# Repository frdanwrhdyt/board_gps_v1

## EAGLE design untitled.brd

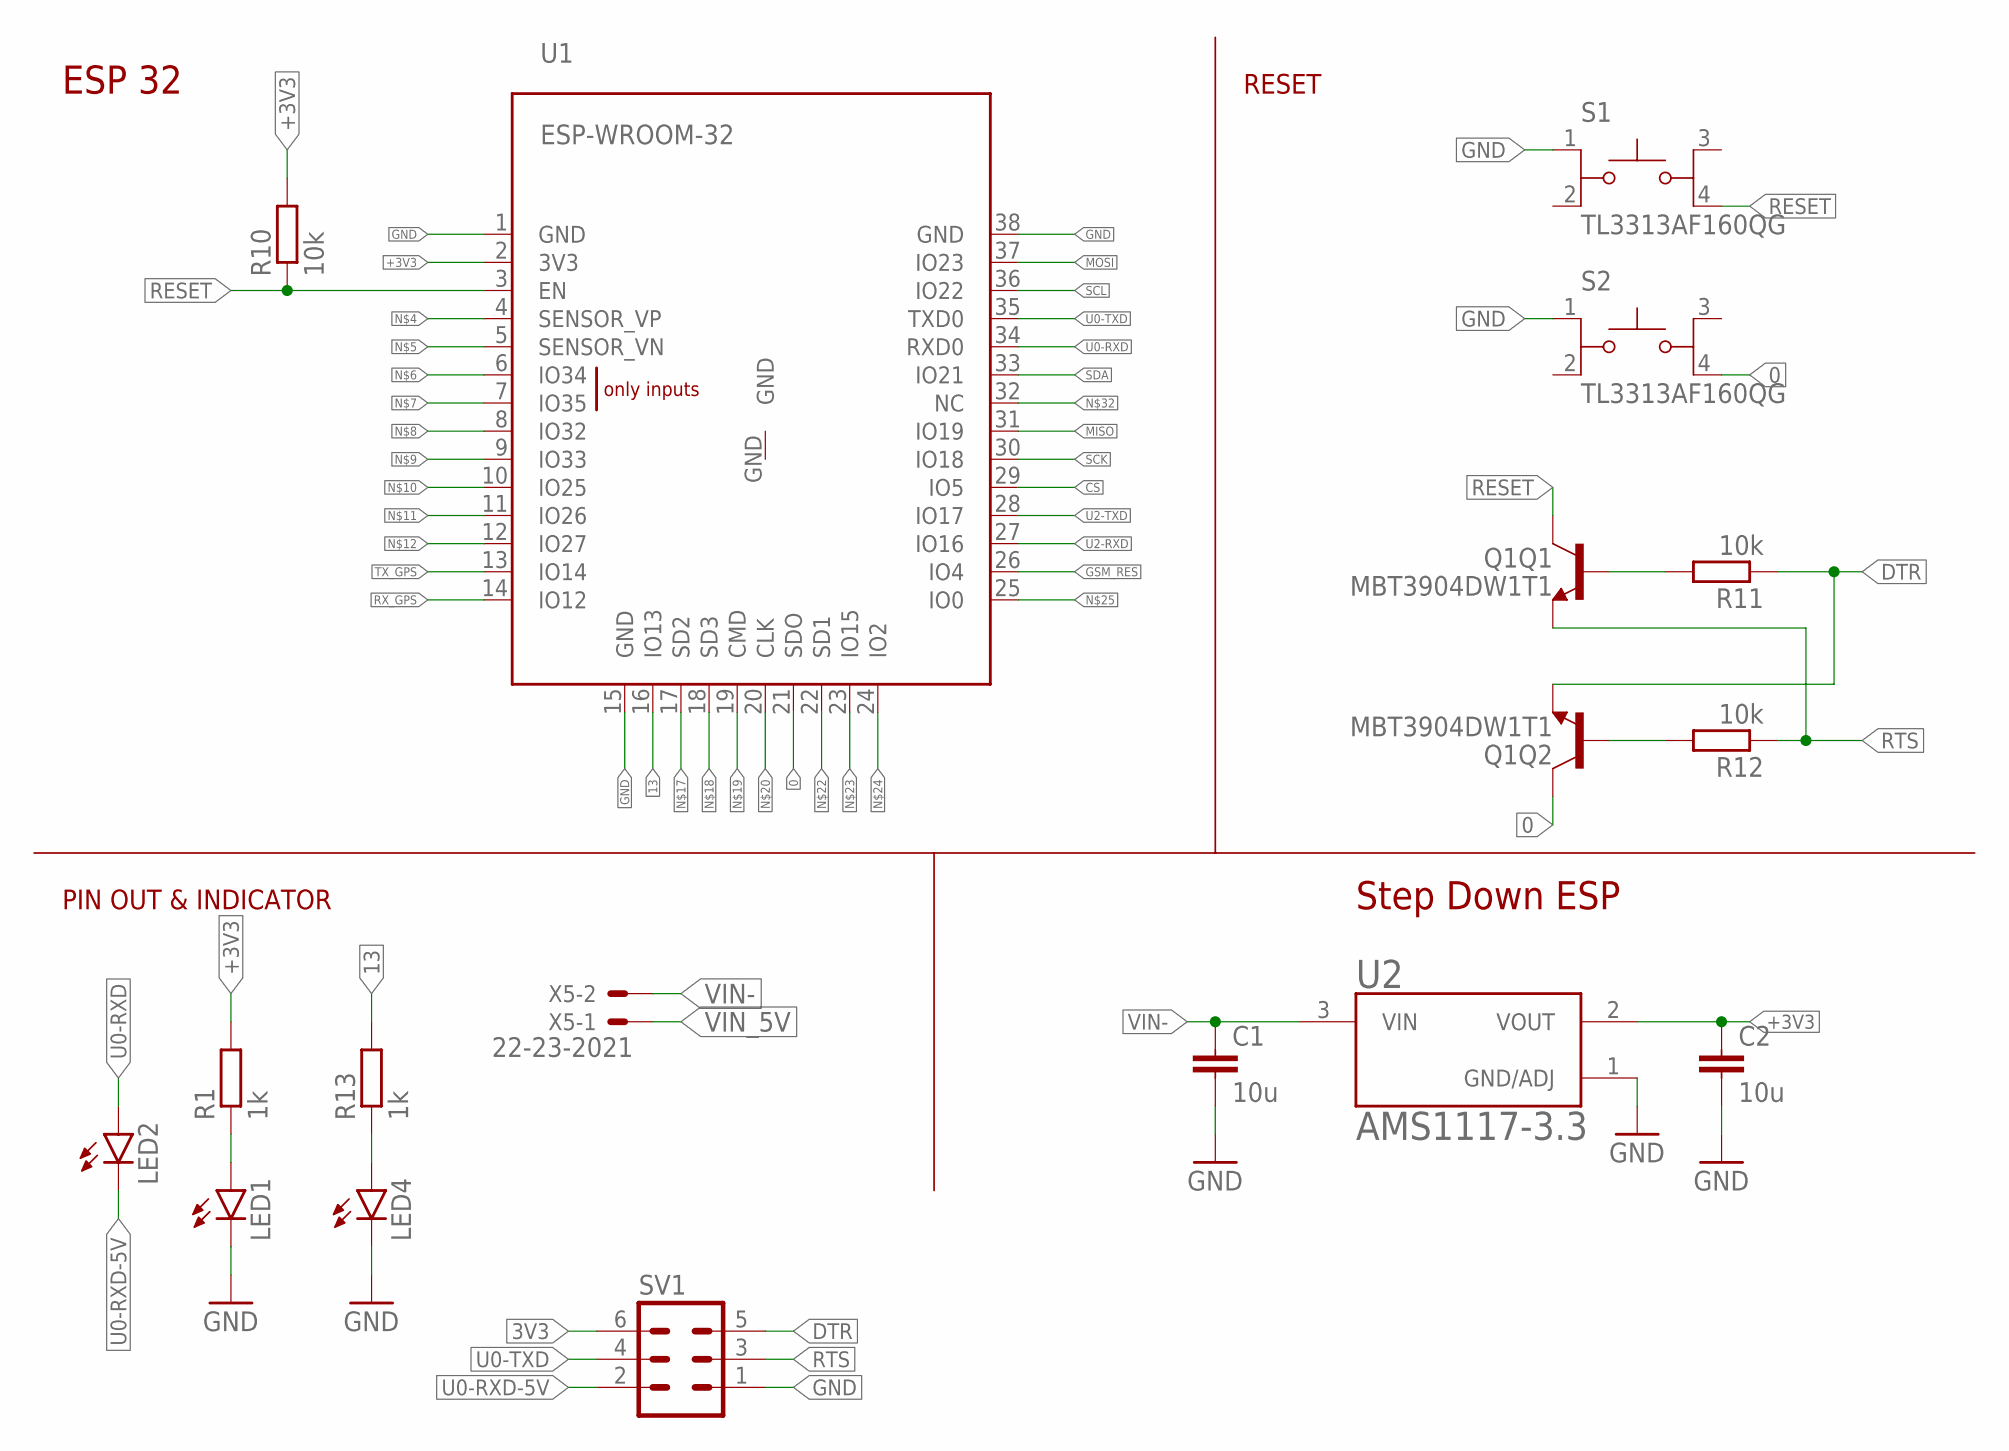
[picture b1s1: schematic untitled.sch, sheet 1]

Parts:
C1, C2: 10u; C0805K
LED1, LED2, LED4: LEDCHIPLED_0805; CHIPLED_0805
Q1: MBT3904DW1T1; SC70-6
R1, R13: 1k; M0805
R10, R11, R12: 10k; M0805
S1, S2: TL3313AF160QG; SW_TL3313AF160QG
SV1: MA03-2
U1: ESP-WROOM-32
U2: AMS1117-3.3; SOT229P700X180-4N
X5: 22-23-2021

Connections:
0: Q1.6 (C), S2.4, U1.21 (SDO)
3V3: SV1.6
13: R13.2, U1.16 (IO13)
+3V3: C2.1, R1.2, R10.2, U1.2 (3V3), U2.2 (VOUT)
CS: U1.29 (IO5); also elsewhere on the board
DTR: Q1.1 (E), R11.1, SV1.5
GND: C1.2, C2.2, LED1.C, LED4.C, S1.1, S2.1, SV1.1, U1.1 (GND), U1.15 (GND), U1.38 (GND), U2.1 (GND/ADJ); also elsewhere on the board
GSM_RES: U1.26 (IO4); also elsewhere on the board
MISO: U1.31 (IO19); also elsewhere on the board
MOSI: U1.37 (IO23); also elsewhere on the board
unnamed: LED1.A, R1.1
unnamed: LED4.A, R13.1
unnamed: Q1.2 (B), R12.2
unnamed: Q1.5 (B), R11.2
RESET: Q1.3 (C), R10.1, S1.4, U1.3 (EN)
RTS: Q1.4 (E), R12.1, SV1.3
RX_GPS: U1.14 (IO12); also elsewhere on the board
SCK: U1.30 (IO18); also elsewhere on the board
SCL: U1.36 (IO22); also elsewhere on the board
SDA: U1.33 (IO21); also elsewhere on the board
TX_GPS: U1.13 (IO14); also elsewhere on the board
U0-RXD: LED2.A, U1.34 (RXD0)
U0-RXD-5V: LED2.C, SV1.2
U0-TXD: SV1.4, U1.35 (TXD0)
U2-RXD: U1.27 (IO16); also elsewhere on the board
U2-TXD: U1.28 (IO17); also elsewhere on the board
VIN-: C1.1, U2.3 (VIN), X5.2; also elsewhere on the board
VIN_5V: X5.1; also elsewhere on the board

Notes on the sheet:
Step Down ESP
ESP 32
RESET
PIN OUT & INDICATOR

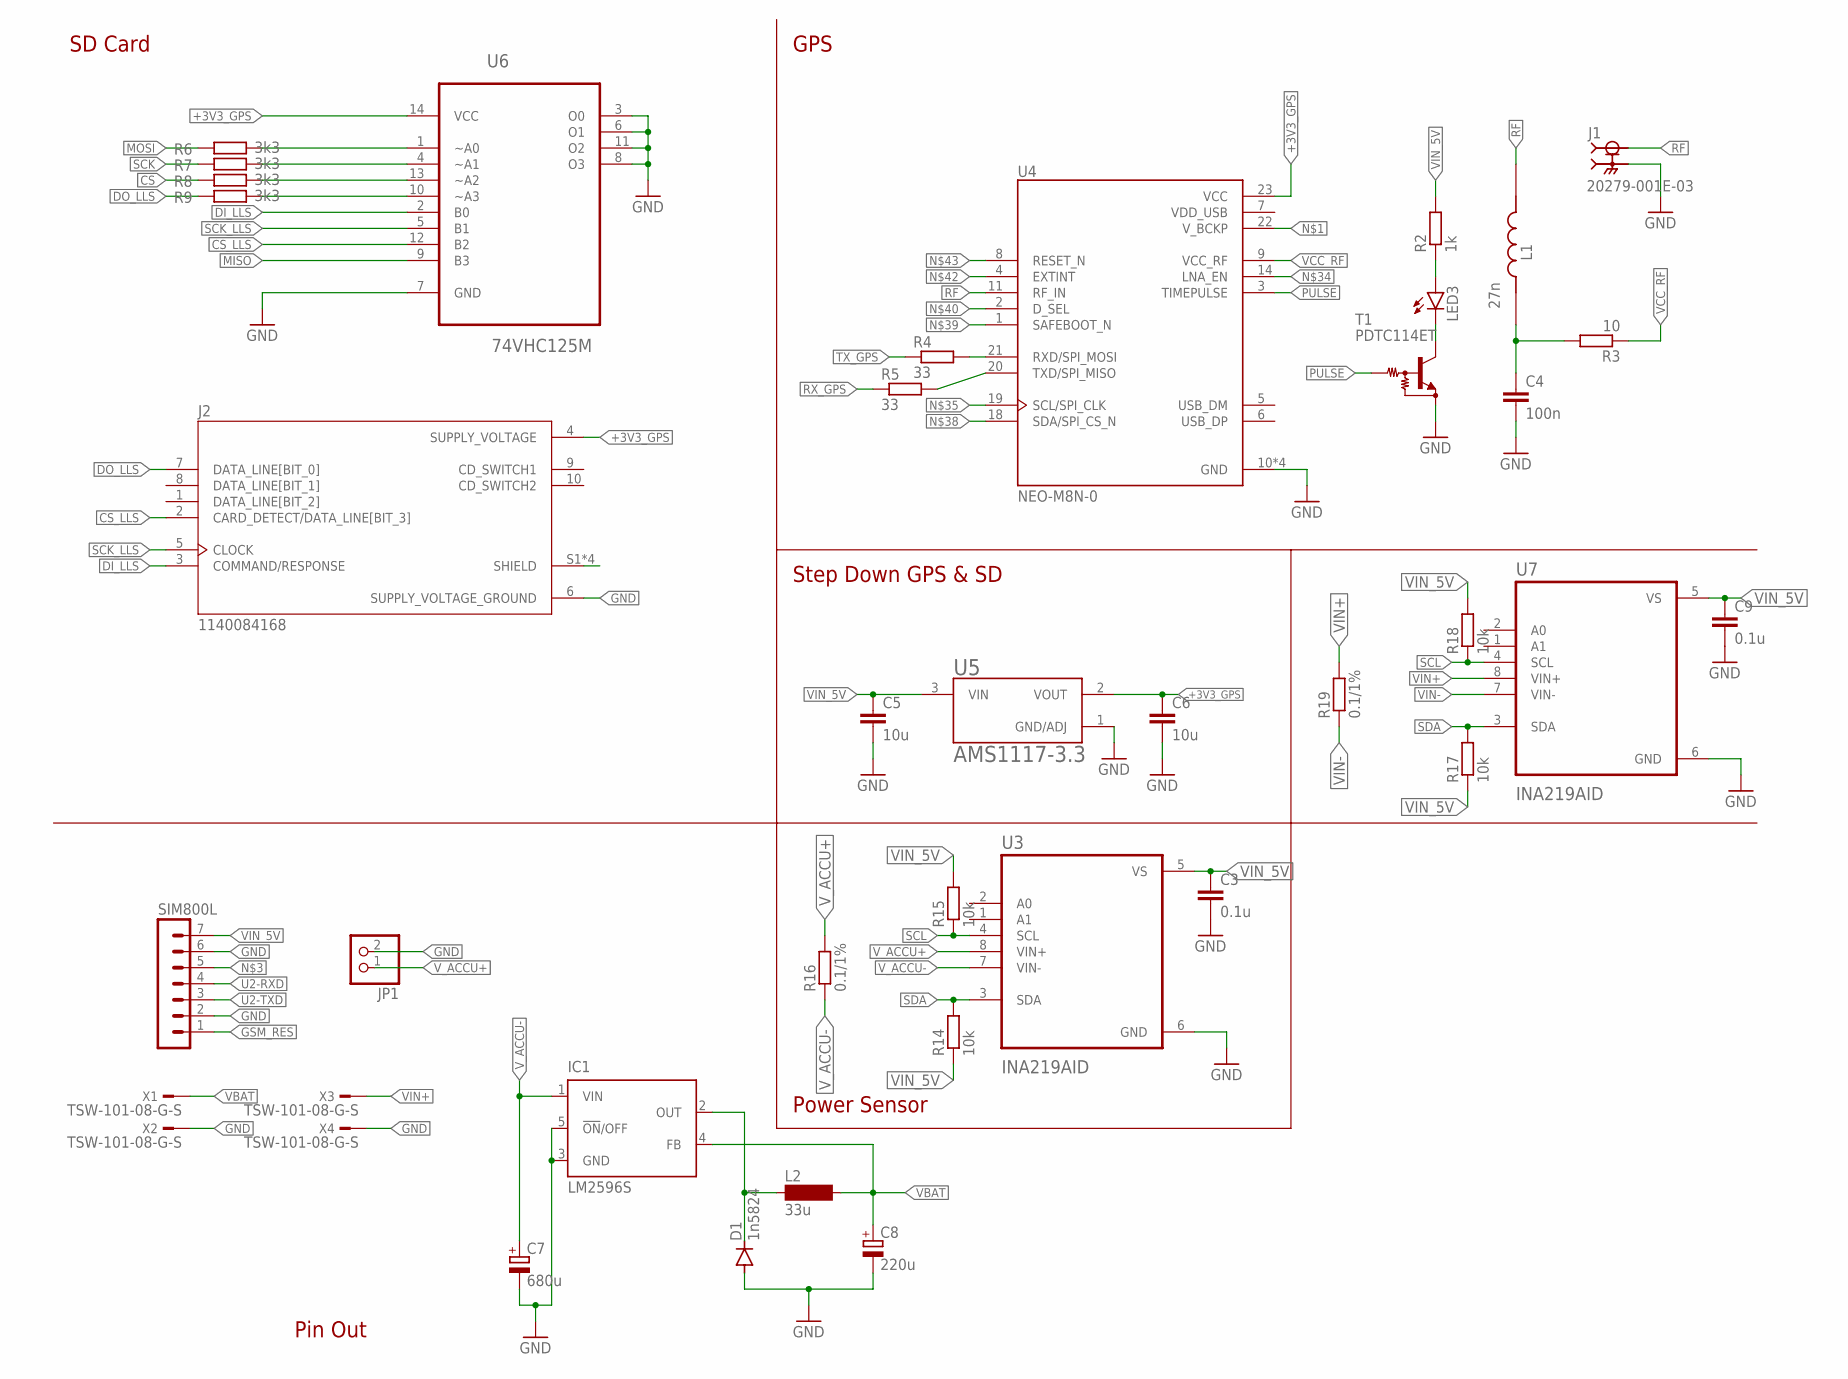
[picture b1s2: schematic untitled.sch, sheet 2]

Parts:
C3, C9: 0.1u; C0805
C4: 100n; C0603K
C5, C6: 10u; C0805K
C7: 680u; 153CLV-0605
C8: 220u; 153CLV-0605
D1: 1n5824; DO-214AC
IC1: LM2596S; TO263-5
J1: 20279-001E-03; IPEX_20279-001E-03
J2: 1140084168; AMPHENOL_1140084168
JP1: PINHD-1X2; 1X02
L1: 27n; INDC2012X105N
L2: 33u; MS85
LED3: LEDCHIPLED_0805; CHIPLED_0805
R2: 1k; M0805
R3: 10; M1206
R4, R5: 33; R1206
R6, R7, R8, R9: 3k3; M0805
R14, R15, R17, R18: 10k; M0805
R16, R19: 0.1/1%; M1206
SIM800L: MA07-1
T1: PDTC114ET; SC59-BEC
U3, U7: INA219AID; SOIC127P599X175-8N
U4: NEO-M8N-0; XCVR_NEO-M8N-0
U5: AMS1117-3.3; SOT229P700X180-4N
U6: 74VHC125M; SOIC127P600X175-14N
X1, X2, X3, X4: TSW-101-08-G-S; TSW-101-XX-G-S

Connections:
+3V3_GPS: C6.1, J2.4 (SUPPLY_VOLTAGE), U4.23 (VCC), U5.2 (VOUT), U6.14 (VCC)
CS: R8.1; also elsewhere on the board
CS_LLS: J2.2 (CARD_DETECT/DATA_LINE[BIT_3]), U6.12 (B2)
DI_LLS: J2.3 (COMMAND/RESPONSE), U6.2 (B0)
DO_LLS: J2.7 (DATA_LINE[BIT_0]), R9.1
GND: C3.2, C4.2, C5.2, C6.2, C7.-, C8.-, C9.2, D1.A, IC1.3 (GND), IC1.5 (!ON!/OFF), J1.2 (GND), J1.3 (GND), J2.6 (SUPPLY_VOLTAGE_GROUND), JP1.2, SIM800L.2, SIM800L.6, T1.E, U3.6 (GND), U4.10 (GND), U4.12 (GND), U4.13 (GND), U4.24 (GND), U5.1 (GND/ADJ), U6.3 (O0), U6.6 (O1), U6.7 (GND), U6.8 (O3), U6.11 (O2), U7.6 (GND), X2.1, X4.1; also elsewhere on the board
GSM_RES: SIM800L.1; also elsewhere on the board
MISO: U6.9 (B3); also elsewhere on the board
MOSI: R6.1; also elsewhere on the board
unnamed: LED3.A, R2.1
unnamed: LED3.C, T1.C
unnamed: J2.S1 (SHIELD), J2.S2 (SHIELD), J2.S3 (SHIELD), J2.S4 (SHIELD)
unnamed: R5.2, U4.20 (TXD/SPI_MISO)
unnamed: R4.2, U4.21 (RXD/SPI_MOSI)
unnamed: D1.C, IC1.2 (OUT), L2.1
unnamed: R9.2, U6.10 (~A3)
unnamed: R8.2, U6.13 (~A2)
unnamed: R7.2, U6.4 (~A1)
unnamed: R6.2, U6.1 (~A0)
PULSE: T1.B, U4.3 (TIMEPULSE)
RF: J1.1 (SIG), L1.2, U4.11 (RF_IN)
RF_: C4.1, L1.1, R3.2
RX_GPS: R5.1; also elsewhere on the board
SCK: R7.1; also elsewhere on the board
SCK_LLS: J2.5 (CLOCK), U6.5 (B1)
SCL: R15.1, R18.1, U3.4 (SCL), U7.4 (SCL); also elsewhere on the board
SDA: R14.2, R17.2, U3.3 (SDA), U7.3 (SDA); also elsewhere on the board
TX_GPS: R4.1; also elsewhere on the board
U2-RXD: SIM800L.4; also elsewhere on the board
U2-TXD: SIM800L.3; also elsewhere on the board
VBAT: C8.+, IC1.4 (FB), L2.2, X1.1
VCC_RF: R3.1, U4.9 (VCC_RF)
VDD_USB: U4.7 (VDD_USB)
VIN+: R19.2, U7.8 (VIN+), X3.1
VIN-: R19.1, U7.7 (VIN-); also elsewhere on the board
VIN_5V: C3.1, C5.1, C9.1, R2.2, R14.1, R15.2, R17.1, R18.2, SIM800L.7, U3.5 (VS), U5.3 (VIN), U7.5 (VS); also elsewhere on the board
V_ACCU+: JP1.1, R16.2, U3.8 (VIN+)
V_ACCU-: C7.+, IC1.1 (VIN), R16.1, U3.7 (VIN-)

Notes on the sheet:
SD Card
Pin Out
Power Sensor
Step Down GPS & SD
GPS

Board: 2 copper layers, 57 parts (21 on the bottom side), 50 nets, no tracks yet.

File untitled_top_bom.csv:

Comment,Designator,Footprint,LCSC Part #
0.1/1%,R16,M1206,
0.1u,C3,C0805,
1k,R1 R2 R13,M0805,
1n5824,D1,DO-214AC,
10,R3,M1206,
10k,R14 R15,M0805,
10u,C1 C2,C0805K,
27n,L1,INDC2012X105N,
33,R4 R5,R1206,
33u,L2,MS85,
100n,C4,C0603K,
220u,C8,153CLV-0605,
680u,C7,153CLV-0605,
20279-001E-03,J1,IPEX_20279-001E-03,
AMS1117-3.3,U2,SOT229P700X180-4N,
ESP-WROOM-32,U1,ESP-WROOM-32,
INA219AID,U3,SOIC127P599X175-8N,
LM2596S,IC1,TO263-5,
NEO-M8N-0,U4,XCVR_NEO-M8N-0,
PDTC114ET,T1,SC59-BEC,
